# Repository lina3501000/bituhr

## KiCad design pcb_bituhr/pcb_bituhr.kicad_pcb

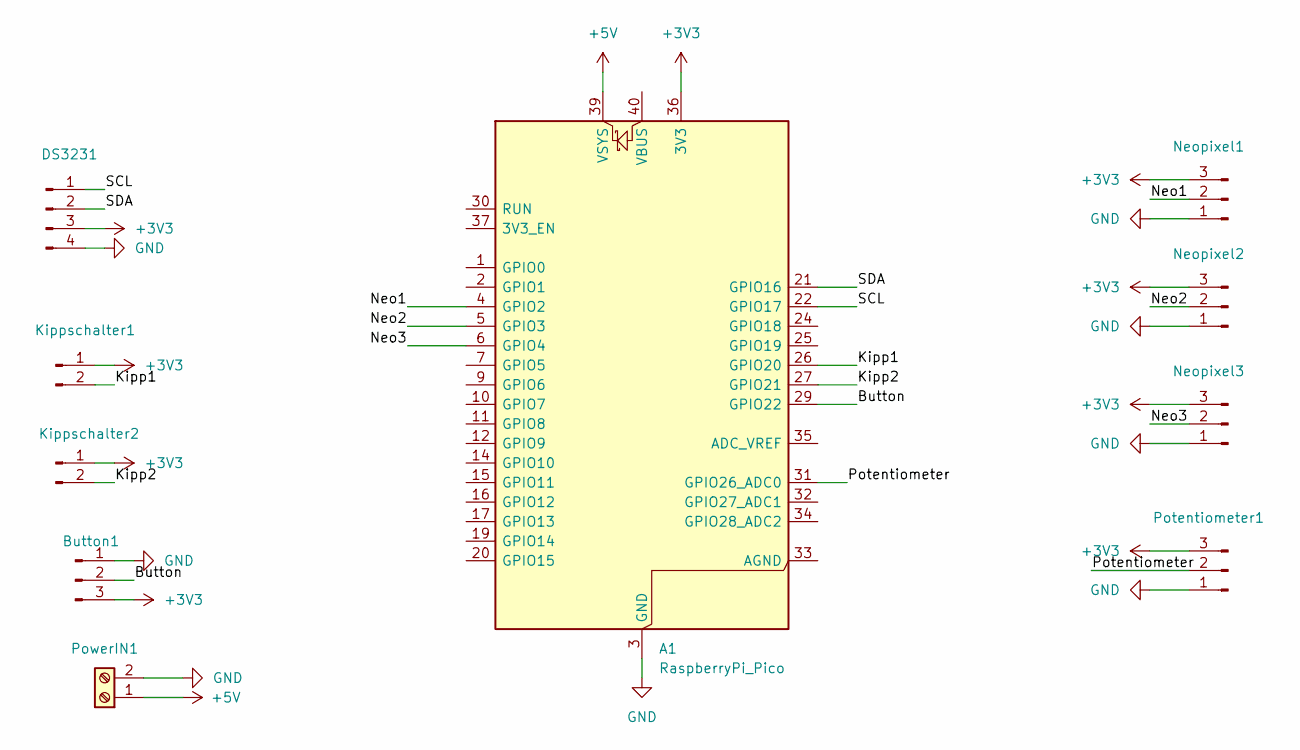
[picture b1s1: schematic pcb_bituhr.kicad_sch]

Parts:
A1: RaspberryPi_Pico; RaspberryPi_Pico_Common_THT
Button1: Conn_01x03_Pin; JST_XH_B3B-XH-A_1x03_P2.50mm_Vertical
DS3231: Conn_01x04_Pin; PinSocket_1x04_P2.54mm_Vertical
Kippschalter1, Kippschalter2: Conn_01x02_Pin; JST_XH_B2B-XH-A_1x02_P2.50mm_Vertical
Neopixel1, Neopixel2, Neopixel3: Conn_01x03_Pin; JST_XH_B3B-XH-A_1x03_P2.50mm_Vertical
Potentiometer1: Conn_01x03_Pin; JST_XH_B3B-XH-A_1x03_P2.50mm_Vertical
PowerIN1: Screw_Terminal_01x02; TerminalBlock_Xinya_XY308-2.54-2P_1x02_P2.54mm_Horizontal

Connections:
+3V3: A1.36 (3V3), Button1.3, DS3231.3, Kippschalter1.1, Kippschalter2.1, Neopixel1.3, Neopixel2.3, Neopixel3.3, Potentiometer1.3
+5V: A1.39 (VSYS), PowerIN1.1
/Button: A1.29 (GPIO22), Button1.2
/Kipp1: A1.26 (GPIO20), Kippschalter1.2
/Kipp2: A1.27 (GPIO21), Kippschalter2.2
/Neo1: A1.4 (GPIO2), Neopixel1.2
/Neo2: A1.5 (GPIO3), Neopixel2.2
/Neo3: A1.6 (GPIO4), Neopixel3.2
/Potentiometer: A1.31 (GPIO26_ADC0), Potentiometer1.2
/SCL: A1.22 (GPIO17), DS3231.1
/SDA: A1.21 (GPIO16), DS3231.2
GND: A1.3 (GND), A1.8 (GND), A1.13 (GND), A1.18 (GND), A1.23 (GND), A1.28 (GND), A1.38 (GND), Button1.1, DS3231.4, Neopixel1.1, Neopixel2.1, Neopixel3.1, Potentiometer1.1, PowerIN1.2

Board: 2 copper layers, 10 parts (0 on the bottom side), 12 nets, no tracks yet.

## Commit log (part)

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2026-03-13 sachen sichern
2026-04-04 .gitignore gemacht
2026-04-04 library hinzugefügt
2026-04-04 test git config
2026-04-04 updated library und main, funktionsweise sichergestellt
2026-04-04 potentiometer für alle fabren hinzugefügt
2026-04-04 hizugefügt: generell schalter für an/aus led
2026-04-04 in kommentar: weitere fahlerhafte version, muss noch funktionabel machen
2026-04-09 einstellung rgb funktioniert
2026-04-09 entprellung geändert. erfolgreich
2026-04-15 Add common environment and virtual environment files to .gitignore
2026-04-15 ordner umbennant
2026-04-15 hinzugefügt: 3 mal auf holz klopfen. noch nicht getestet
2026-04-16 zeitumstellung funktioniert. aber viele # und chaotisch. aufräumen wäre gut
2026-04-16 Ignore ds3231_init.py in .gitignore
2026-04-16 library für zeitumstellung geändert
2026-04-16 unnötige sachen löschen
2026-04-16 nacht modus hinzugefügt
2026-04-16 Ignore bit_uhr_pcb in .gitignore
2026-04-16 in neuen ordner
2026-04-16 irgendwas löschen?
2026-04-16 glaube hier mit lösche ich pcb,... aber kp
2026-04-18 neu strukturiert
2026-04-18 orga zeug
2026-04-18 zeitumstellung als funktion
